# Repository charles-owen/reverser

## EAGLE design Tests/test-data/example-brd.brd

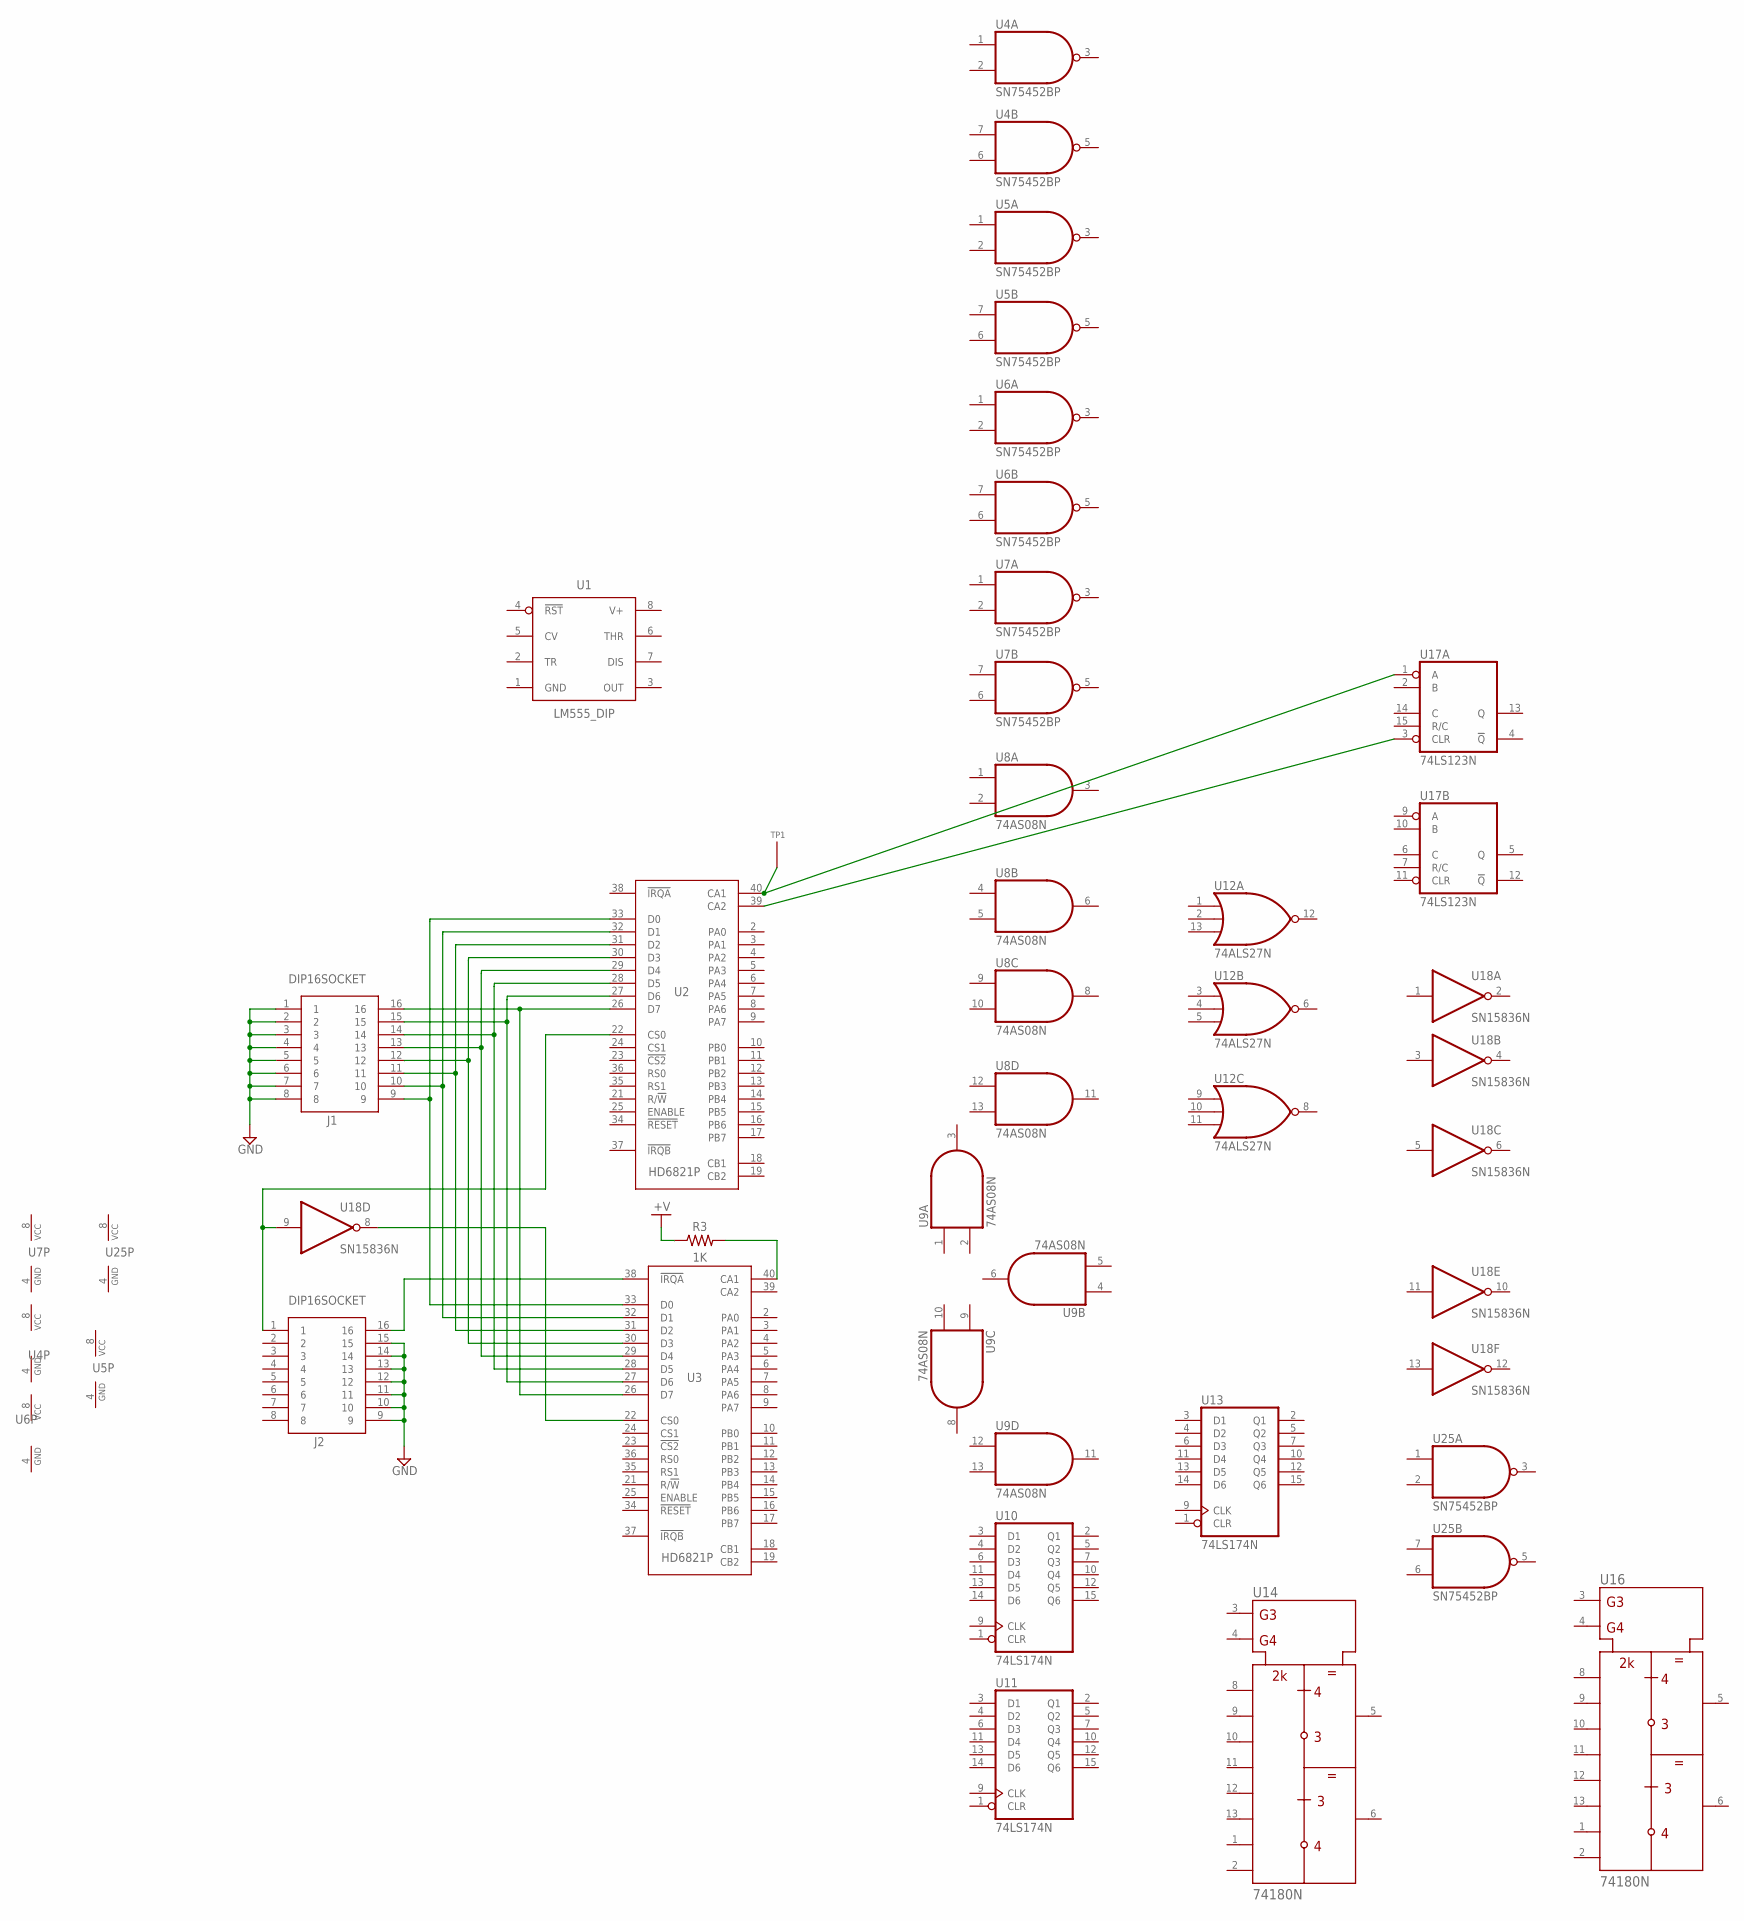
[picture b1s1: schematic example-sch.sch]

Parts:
J1, J2: DIP16SOCKET; DIL16
R3: 1K; RESAD1176W63L850D250B
TP1: TESTPOINT
U1: LM555_DIP; DIP826W53P254L959H508Q8B
U2, U3: HD6821P; DIL40
U4, U5, U6, U7, U25: SN75452BP; DIL08
U8, U9: 74AS08N; DIL14
U10, U11, U13: 74LS174N; DIL16
U12: 74ALS27N; DIL14
U14, U16: 74180N; DIL14
U17: 74LS123N; DIL16
U18: SN15836N; DIL14

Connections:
+UB: U14.14 (+UB), U16.14 (+UB)
+V: R3.1
-UB: U14.7 (-UB), U16.7 (-UB)
GND: J1.1, J1.2, J1.3, J1.4, J1.5, J1.6, J1.7, J1.8, J2.9, J2.10, J2.11, J2.12, J2.13, J2.14, J2.15, U1.1 (GND), U4.4 (GND), U5.4 (GND), U6.4 (GND), U7.4 (GND), U8.7 (GND), U9.7 (GND), U10.8 (GND), U11.8 (GND), U12.7 (GND), U13.8 (GND), U17.8 (GND), U18.7 (GND), U25.4 (GND)
unnamed: J1.9, U2.33 (D0), U3.33 (D0)
unnamed: J1.10, U2.32 (D1), U3.32 (D1)
unnamed: J1.11, U2.31 (D2), U3.31 (D2)
unnamed: J1.12, U2.30 (D3), U3.30 (D3)
unnamed: J1.13, U2.29 (D4), U3.29 (D4)
unnamed: J1.14, U2.28 (D5), U3.28 (D5)
unnamed: J1.15, U2.27 (D6), U3.27 (D6)
unnamed: J1.16, U2.26 (D7), U3.26 (D7)
unnamed: J2.16, U3.38 (!IRQA)
unnamed: U3.22 (CS0), U18.8 (O)
unnamed: TP1.P$1, U2.40 (CA1), U17.1 (A)
unnamed: R3.2, U3.40 (CA1)
unnamed: U2.39 (CA2), U17.3 (CLR)
U17: J2.1, U2.22 (CS0), U18.9 (I)
V+: U1.8 (V+)
VCC: U4.8 (VCC), U5.8 (VCC), U6.8 (VCC), U7.8 (VCC), U8.14 (VCC), U9.14 (VCC), U10.16 (VCC), U11.16 (VCC), U12.14 (VCC), U13.16 (VCC), U17.16 (VCC), U18.14 (VCC), U25.8 (VCC)

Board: 2 copper layers, 22 parts (0 on the bottom side), 18 nets, no tracks yet.

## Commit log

2021-07-21 Working towards final Cmake configuration that works.
2021-07-21 Changes to the way resources are loaded.
2021-12-06 Starting work on the 2.0 approach based on Eagle schematic and board files
2021-12-06 More work on this
2021-12-06 Design updates
2021-12-07 shc and brd file management
2021-12-08 Save/Load functionality for Design is now working
2021-12-09 Views are coming back online
2021-12-11 PCB display is working
2021-12-12 Loads the .brd file and displays component names
2021-12-12 Displays components
2021-12-12 Old file cleanout
2021-12-13 All attributes displayed.
2021-12-13 User interface improvements
2021-12-17 Now able to select and move elements on the board
2021-12-19 Symbols and DeviceSets are now loaded
2021-12-20 Parts now loaded. Ability to find Instance from pad number
2021-12-21 Networks loaded from schematic file
2021-12-22 Networks and component positions working
